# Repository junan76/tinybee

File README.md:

# TINYBEE

This repository contains the hardware design of tinybeef405 flight controller, It supports the latest betaflight firmware currently, you can build your own firmware with the configuration files in the `configs` directory, see the details below.

I personally use this flight controller board as a hardware platform to learn betafight source code and stm32 microcontrollers, related videos were posted on my [Bilibili](https://space.bilibili.com/258537970) account.

## Hardware and Features

- MCU: STM32F405
- IMU: ICM42688-P
- BARO: BMP280
- OSD: BetaFlight OSD, AT7456E
- Blackbox: 128MiB onboard flash, W25Q128JVSIQ
- UARTS: UART2/UART4/UART5
- SWD: Yes
- Digital VTX: Yes
- LEDs: LED0/LED1
- LED Strip: Yes
- Beeper: Yes
- Boot button: For easy entry into DFU mode

## Firmware build and flash

1. Get the latest betaflight source code

```shell
$ git clone https://github.com/betaflight/betaflight.git
$ cd betaflight
$ git submodule init && git submodule update --recursive
```

2. Copy config files

```shell
# download tinybee first, and then...
$ cp -r tinybee/configs/TNBF405 betaflight/src/config/configs
```

3. Build firmware

```shell
$ cd betaflight
$ make arm_sdk_install
$ make TNBF405
# wait until make completes its job, you will get:
$ ls obj
betaflight_2025.12.0-beta_STM32F405_TNBF405.hex  main
# "betaflight_2025.12.0-beta_STM32F405_TNBF405.hex" is what you need
```
4. Flash firmware

    - With [Betaflight Configurator](https://github.com/betaflight/betaflight-configurator/releases) properly installed and opened

    - Connect tinybee flight controlelr via usb

    - Enter DFU mode, press and hold the `BOOT` button, then press the `RESET` button

    - Go to the `Firmware Flasher` tab

    - Load local firmware then flash firmware

5. Basic configurations

    You need to do at least the following setups so that your drone works.

    - `Ports`: select the right ports for RX and VTX
    - `Motors`: make sure the order and direction are both ok
    - `Modes`: how to arm your drone and switch to other modes
    - `VTX`: analog or digital
    - `OSD`: analog or digital

    For more information see [the betalfight wiki](https://www.betaflight.com/docs/wiki/getting-started/setup-guide).
    
    If everything goes well, the final result will be like this:

## Special Thanks

- [The original AcciF405 FC Design](https://oshwlab.com/jesuslg123/f4-v1)
- [Betaflight Project](https://www.betaflight.com/)

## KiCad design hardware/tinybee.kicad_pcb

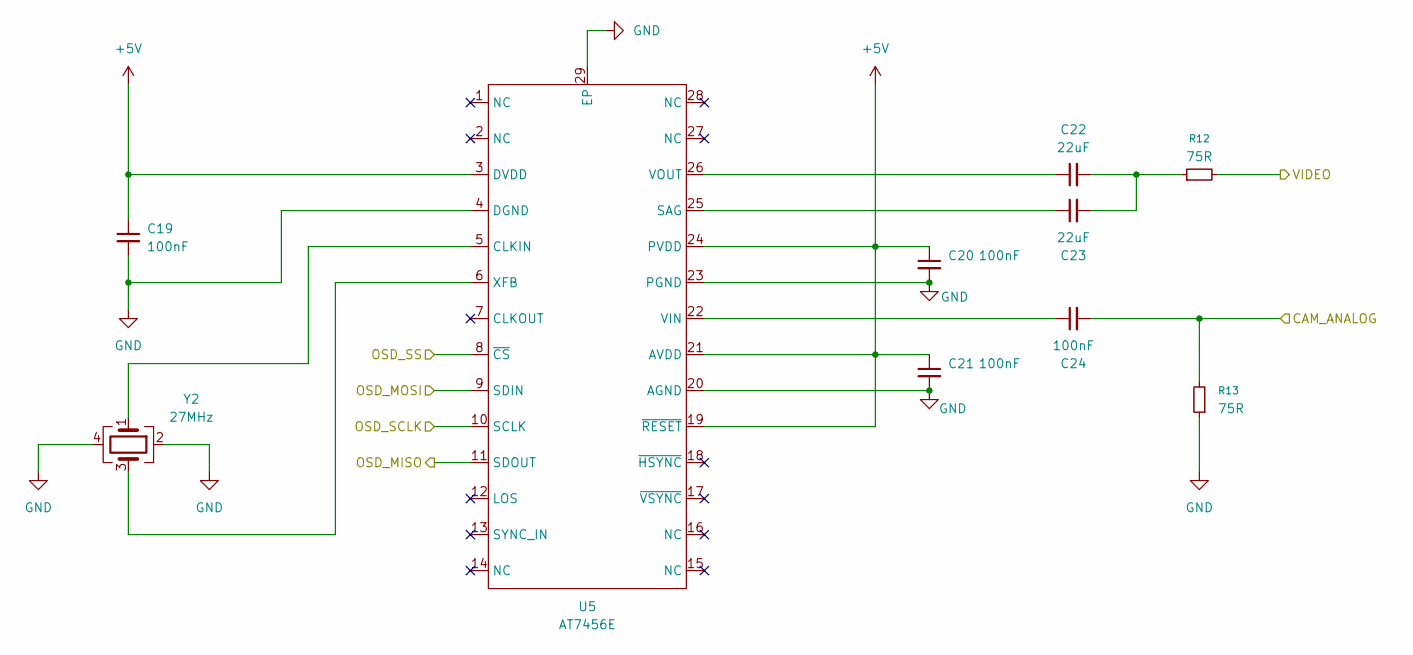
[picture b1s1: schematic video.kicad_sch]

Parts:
C19, C20, C21, C24: 100nF; C_0402_1005Metric; MPN C361198
C22, C23: 22uF; C_0603_1608Metric; MPN C2762594
R12, R13: 75R; R_0402_1005Metric; MPN C25133
U5: AT7456E; TSSOP-28-1EP_4.4x9.7mm_P0.65mm_EP2.85x6.7mm; MPN C82351
Y2: 27MHz; Crystal_SMD_3225-4Pin_3.2x2.5mm; MPN C9008

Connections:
+5V: C19.1, C20.1, C21.1, U5.3 (DVDD), U5.19 (~RESET), U5.21 (AVDD), U5.24 (PVDD); also elsewhere on the board
/CONNECTORS/CAM_ANALOG: C24.2, R13.2; also elsewhere on the board
/CONNECTORS/VIDEO: R12.2; also elsewhere on the board
/MCU/OSD_MISO: U5.11 (SDOUT); also elsewhere on the board
/MCU/OSD_MOSI: U5.9 (SDIN); also elsewhere on the board
/MCU/OSD_SCLK: U5.10 (SCLK); also elsewhere on the board
/MCU/OSD_SS: U5.8 (~CS); also elsewhere on the board
GND: C19.2, C20.2, C21.2, R13.1, U5.4 (DGND), U5.20 (AGND), U5.23 (PGND), U5.29 (EP), Y2.2, Y2.4; also elsewhere on the board
unnamed: C22.2, C23.2, R12.1
unnamed: U5.5 (CLKIN), Y2.1
unnamed: C23.1, U5.25 (SAG)
unnamed: C24.1, U5.22 (VIN)
unnamed: C22.1, U5.26 (VOUT)
unnamed: U5.6 (XFB), Y2.3

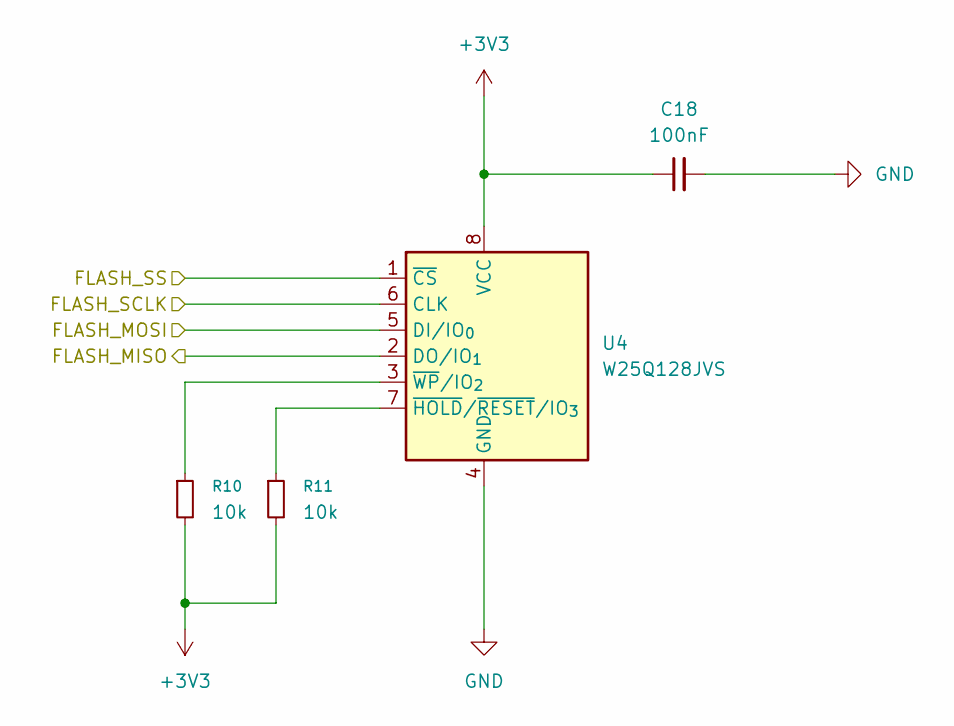
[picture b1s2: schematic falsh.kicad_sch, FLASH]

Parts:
C18: 100nF; C_0402_1005Metric; MPN C361198
R10, R11: 10k; R_0402_1005Metric; MPN C25744
U4: W25Q128JVS; SOIC-8_5.3x5.3mm_P1.27mm; MPN C113767

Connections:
+3V3: C18.1, R10.2, R11.2, U4.8 (VCC); also elsewhere on the board
/FLASH/FLASH_MISO: U4.2 (DO/IO_{1}); also elsewhere on the board
/FLASH/FLASH_MOSI: U4.5 (DI/IO_{0}); also elsewhere on the board
/FLASH/FLASH_SCLK: U4.6 (CLK); also elsewhere on the board
/FLASH/FLASH_SS: U4.1 (~CS); also elsewhere on the board
GND: C18.2, U4.4 (GND); also elsewhere on the board
unnamed: R11.1, U4.7 (~HOLD/~RESET/IO_{3})
unnamed: R10.1, U4.3 (~WP/IO_{2})

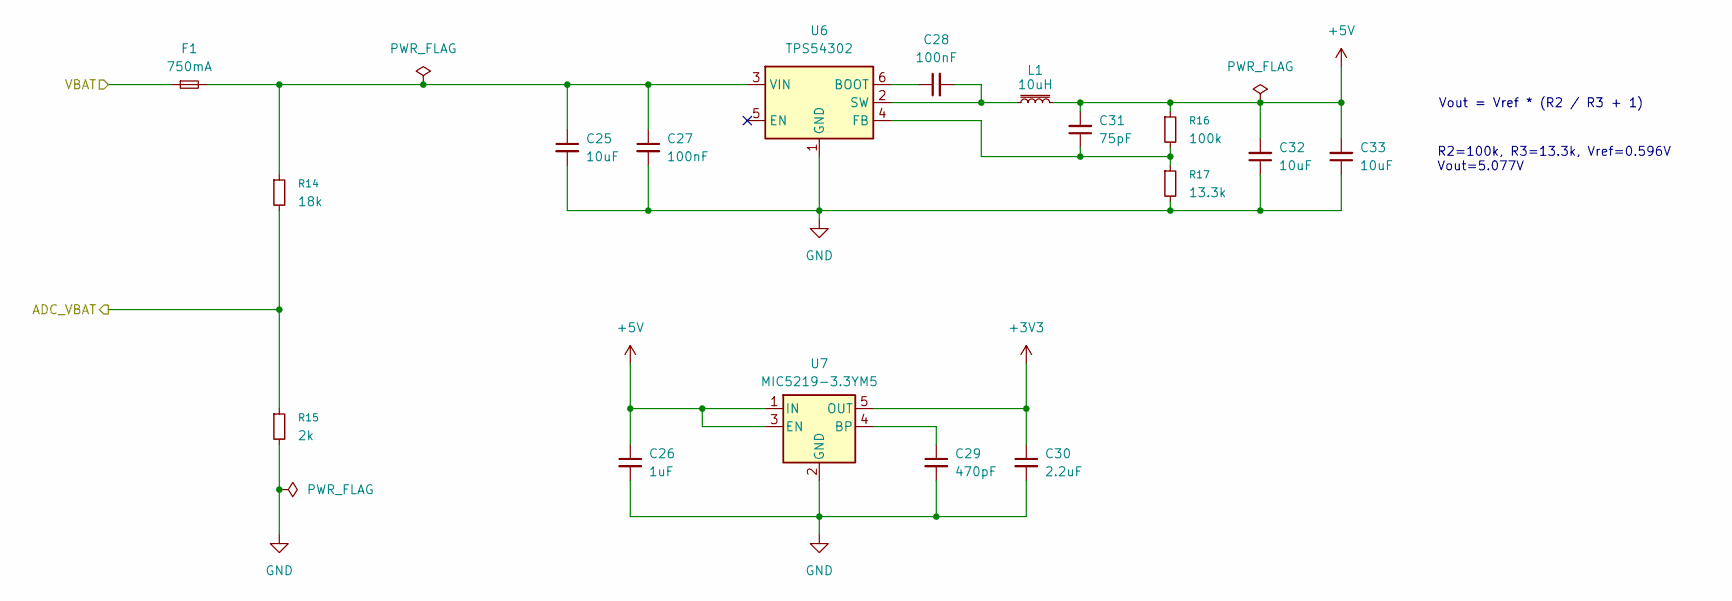
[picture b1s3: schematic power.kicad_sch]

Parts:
C25, C32, C33: 10uF; C_0402_1005Metric; MPN C7472949
C26: 1uF; C_0402_1005Metric; MPN C52923
C27, C28: 100nF; C_0402_1005Metric; MPN C361198
C29: 470pF; C_0402_1005Metric; MPN C1537
C30: 2.2uF; C_0402_1005Metric; MPN C76595
C31: 75pF; C_0402_1005Metric; MPN C107010
F1: 750mA; Fuse_1206_3216Metric; MPN C187594
L1: 10uH; L_Changjiang_FXL0630; MPN C167223
R14: 18k; R_0402_1005Metric; MPN C25762
R15: 2k; R_0402_1005Metric; MPN C4109
R16: 100k; R_0402_1005Metric; MPN C25741
R17: 13.3k; R_0402_1005Metric; MPN C122547
U6: TPS54302; SOT-23-6; MPN C311983
U7: MIC5219-3.3YM5; SOT-23-5; MPN C29613

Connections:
+3V3: C30.1, U7.5 (OUT); also elsewhere on the board
+5V: C26.1, C31.2, C32.2, C33.2, L1.2, R16.1, U7.1 (IN), U7.3 (EN); also elsewhere on the board
/CONNECTORS/VBAT: F1.1; also elsewhere on the board
/MCU/ADC_VBAT: R14.2, R15.1; also elsewhere on the board
GND: C25.2, C26.2, C27.2, C29.2, C30.2, C32.1, C33.1, R15.2, R17.2, U6.1 (GND), U7.2 (GND); also elsewhere on the board
unnamed: C28.1, U6.6 (BOOT)
unnamed: C31.1, R16.2, R17.1, U6.4 (FB)
unnamed: C28.2, L1.1, U6.2 (SW)
unnamed: C25.1, C27.1, F1.2, R14.1, U6.3 (VIN)
unnamed: C29.1, U7.4 (BP)

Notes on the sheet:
R2=100k, R3=13.3k, Vref=0.596V Vout=5.077V
Vout = Vref * (R2 / R3 + 1)

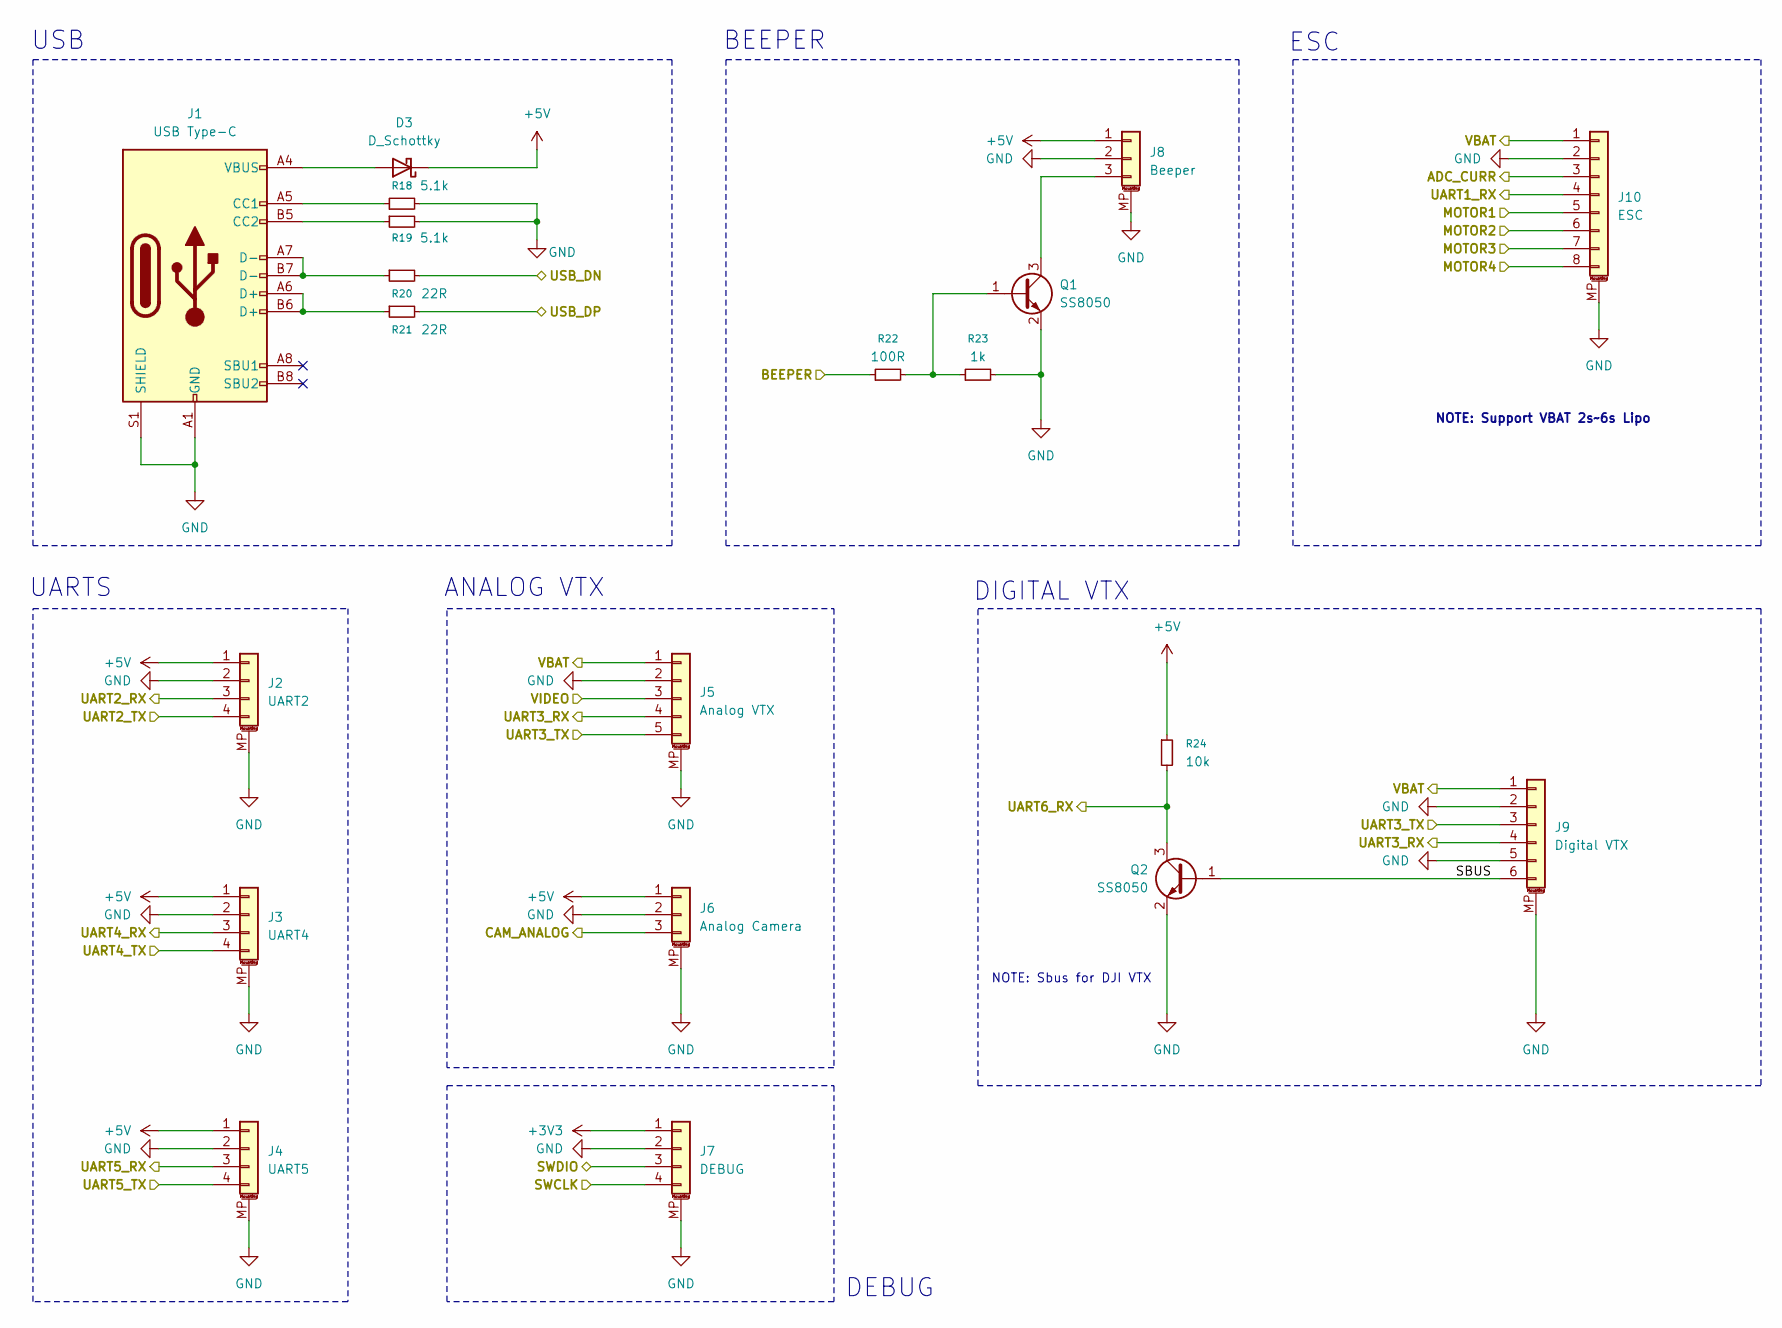
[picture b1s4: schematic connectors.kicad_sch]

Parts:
D3: D_Schottky; D_SMA; MPN C7420369
J1: USB Type-C; USB_C_Receptacle_HCTL_HC-TYPE-C-16P-01A; MPN C3148200
J2: UART2; JST_SH_SM04B-SRSS-TB_1x04-1MP_P1.00mm_Horizontal; MPN C3029343
J3: UART4; JST_SH_SM04B-SRSS-TB_1x04-1MP_P1.00mm_Horizontal; MPN C3029343
J4: UART5; JST_SH_SM04B-SRSS-TB_1x04-1MP_P1.00mm_Horizontal; MPN C3029343
J5: Analog VTX; JST_SH_SM05B-SRSS-TB_1x05-1MP_P1.00mm_Horizontal; MPN C3029344
J6: Analog Camera; JST_SH_SM03B-SRSS-TB_1x03-1MP_P1.00mm_Horizontal; MPN C3029342
J7: DEBUG; JST_SH_SM04B-SRSS-TB_1x04-1MP_P1.00mm_Horizontal; MPN C3029343
J8: Beeper; JST_SH_SM03B-SRSS-TB_1x03-1MP_P1.00mm_Horizontal; MPN C3029342
J9: Digital VTX; JST_SH_SM06B-SRSS-TB_1x06-1MP_P1.00mm_Horizontal; MPN C3029345
J10: ESC; JST_SH_SM08B-SRSS-TB_1x08-1MP_P1.00mm_Horizontal; MPN C3029347
Q1, Q2: SS8050; SOT-23; MPN C7420370
R18, R19: 5.1k; R_0402_1005Metric; MPN C25905
R20, R21: 22R; R_0402_1005Metric; MPN C25092
R22: 100R; R_0402_1005Metric; MPN C25076
R23: 1k; R_0402_1005Metric; MPN C11702
R24: 10k; R_0402_1005Metric; MPN C25744

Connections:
+3V3: J7.1; also elsewhere on the board
+5V: D3.1 (K), J2.1, J3.1, J4.1, J6.1, J8.1, R24.1; also elsewhere on the board
/CONNECTORS/ADC_CURR: J10.3; also elsewhere on the board
/CONNECTORS/BEEPER: R22.1; also elsewhere on the board
/CONNECTORS/CAM_ANALOG: J6.3; also elsewhere on the board
/CONNECTORS/MOTOR1: J10.5; also elsewhere on the board
/CONNECTORS/MOTOR2: J10.6; also elsewhere on the board
/CONNECTORS/MOTOR3: J10.7; also elsewhere on the board
/CONNECTORS/MOTOR4: J10.8; also elsewhere on the board
/CONNECTORS/SBUS: J9.6, Q2.1 (B)
/CONNECTORS/SWCLK: J7.4; also elsewhere on the board
/CONNECTORS/SWDIO: J7.3; also elsewhere on the board
/CONNECTORS/UART1_RX: J10.4; also elsewhere on the board
/CONNECTORS/UART2_RX: J2.3; also elsewhere on the board
/CONNECTORS/UART2_TX: J2.4; also elsewhere on the board
/CONNECTORS/UART3_RX: J5.4, J9.4; also elsewhere on the board
/CONNECTORS/UART3_TX: J5.5, J9.3; also elsewhere on the board
/CONNECTORS/UART4_RX: J3.3; also elsewhere on the board
/CONNECTORS/UART4_TX: J3.4; also elsewhere on the board
/CONNECTORS/UART5_RX: J4.3; also elsewhere on the board
/CONNECTORS/UART5_TX: J4.4; also elsewhere on the board
/CONNECTORS/UART6_RX: Q2.3 (C), R24.2; also elsewhere on the board
/CONNECTORS/USB_DN: R20.2; also elsewhere on the board
/CONNECTORS/USB_DP: R21.2; also elsewhere on the board
/CONNECTORS/VBAT: J5.1, J9.1, J10.1; also elsewhere on the board
/CONNECTORS/VIDEO: J5.3; also elsewhere on the board
GND: J1.A1 (GND), J1.A12 (GND), J1.B1 (GND), J1.B12 (GND), J1.S1 (SHIELD), J2.2, J2.MP (MountPin), J3.2, J3.MP (MountPin), J4.2, J4.MP (MountPin), J5.2, J5.MP (MountPin), J6.2, J6.MP (MountPin), J7.2, J7.MP (MountPin), J8.2, J8.MP (MountPin), J9.2, J9.5, J9.MP (MountPin), J10.2, J10.MP (MountPin), Q1.2 (E), Q2.2 (E), R18.2, R19.2, R23.2; also elsewhere on the board
unnamed: D3.2 (A), J1.A4 (VBUS), J1.A9 (VBUS), J1.B4 (VBUS), J1.B9 (VBUS)
unnamed: J1.A5 (CC1), R18.1
unnamed: J1.B5 (CC2), R19.1
unnamed: J1.A6 (D+), J1.B6 (D+), R21.1
unnamed: J1.A7 (D-), J1.B7 (D-), R20.1
unnamed: J8.3, Q1.3 (C)
unnamed: Q1.1 (B), R22.2, R23.1

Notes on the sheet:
ANALOG VTX
DEBUG
DIGITAL VTX
BEEPER
USB
ESC
UARTS
NOTE: Sbus for DJI VTX
NOTE: Support VBAT 2s~6s Lipo

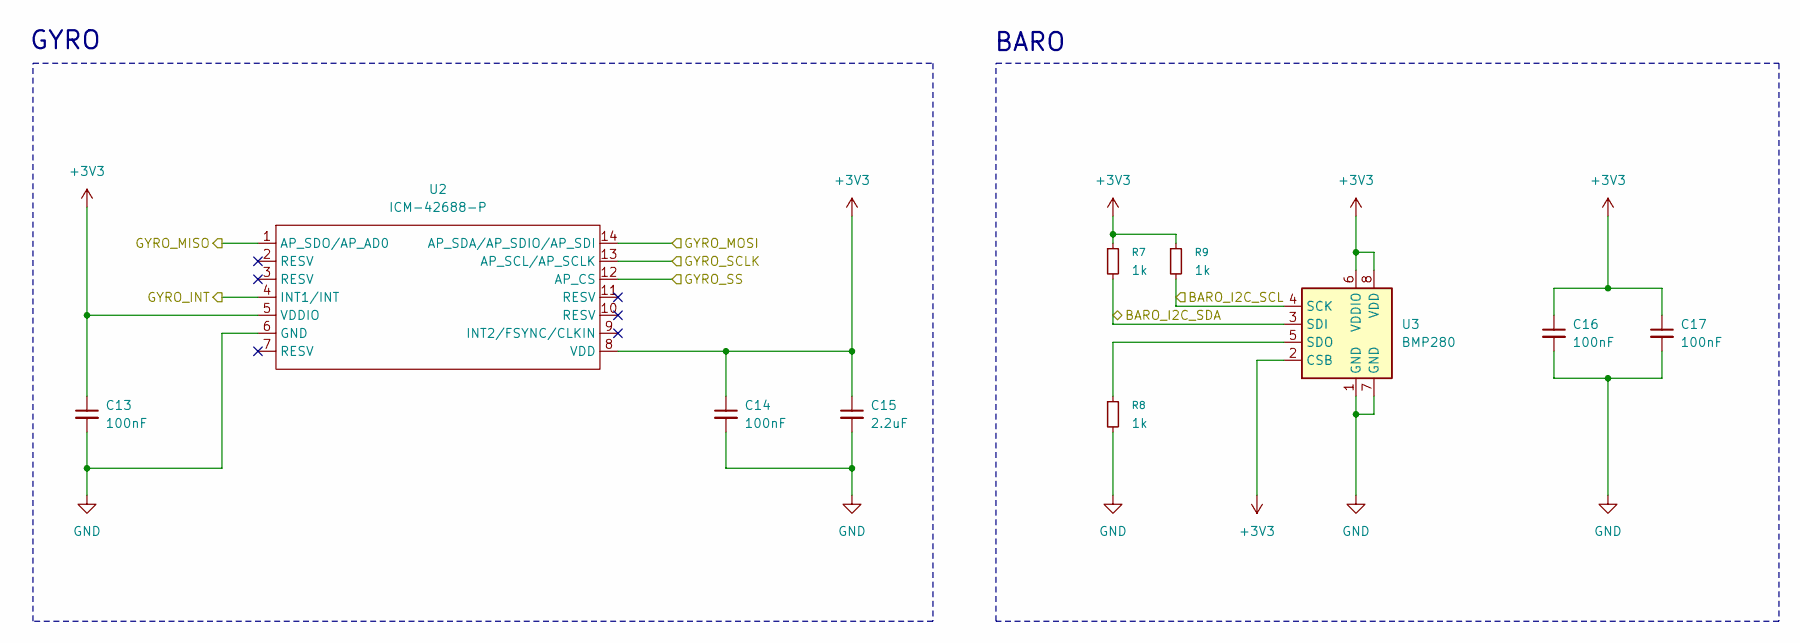
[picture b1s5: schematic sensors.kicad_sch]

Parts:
C13, C14, C16, C17: 100nF; C_0402_1005Metric; MPN C361198
C15: 2.2uF; C_0402_1005Metric; MPN C76595
R7, R8, R9: 1k; R_0402_1005Metric; MPN C11702
U2: ICM-42688-P; LGA-14_3x2.5mm_P0.5mm_LayoutBorder3x4y; MPN C1850418
U3: BMP280; Bosch_LGA-8_2x2.5mm_P0.65mm_ClockwisePinNumbering; MPN C83291

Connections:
+3V3: C13.1, C14.1, C15.1, C16.1, C17.1, R7.1, R9.1, U2.5 (VDDIO), U2.8 (VDD), U3.2 (CSB), U3.6 (VDDIO), U3.8 (VDD); also elsewhere on the board
/MCU/GYRO_INT: U2.4 (INT1/INT); also elsewhere on the board
/MCU/GYRO_MISO: U2.1 (AP_SDO/AP_AD0); also elsewhere on the board
/MCU/GYRO_MOSI: U2.14 (AP_SDA/AP_SDIO/AP_SDI); also elsewhere on the board
/MCU/GYRO_SCLK: U2.13 (AP_SCL/AP_SCLK); also elsewhere on the board
/MCU/GYRO_SS: U2.12 (AP_CS); also elsewhere on the board
/MCU/I2C1_SCL: R9.2, U3.4 (SCK); also elsewhere on the board
/MCU/I2C1_SDA: R7.2, U3.3 (SDI); also elsewhere on the board
GND: C13.2, C14.2, C15.2, C16.2, C17.2, R8.2, U2.6 (GND), U3.1 (GND), U3.7 (GND); also elsewhere on the board
unnamed: R8.1, U3.5 (SDO)

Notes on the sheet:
BARO
GYRO

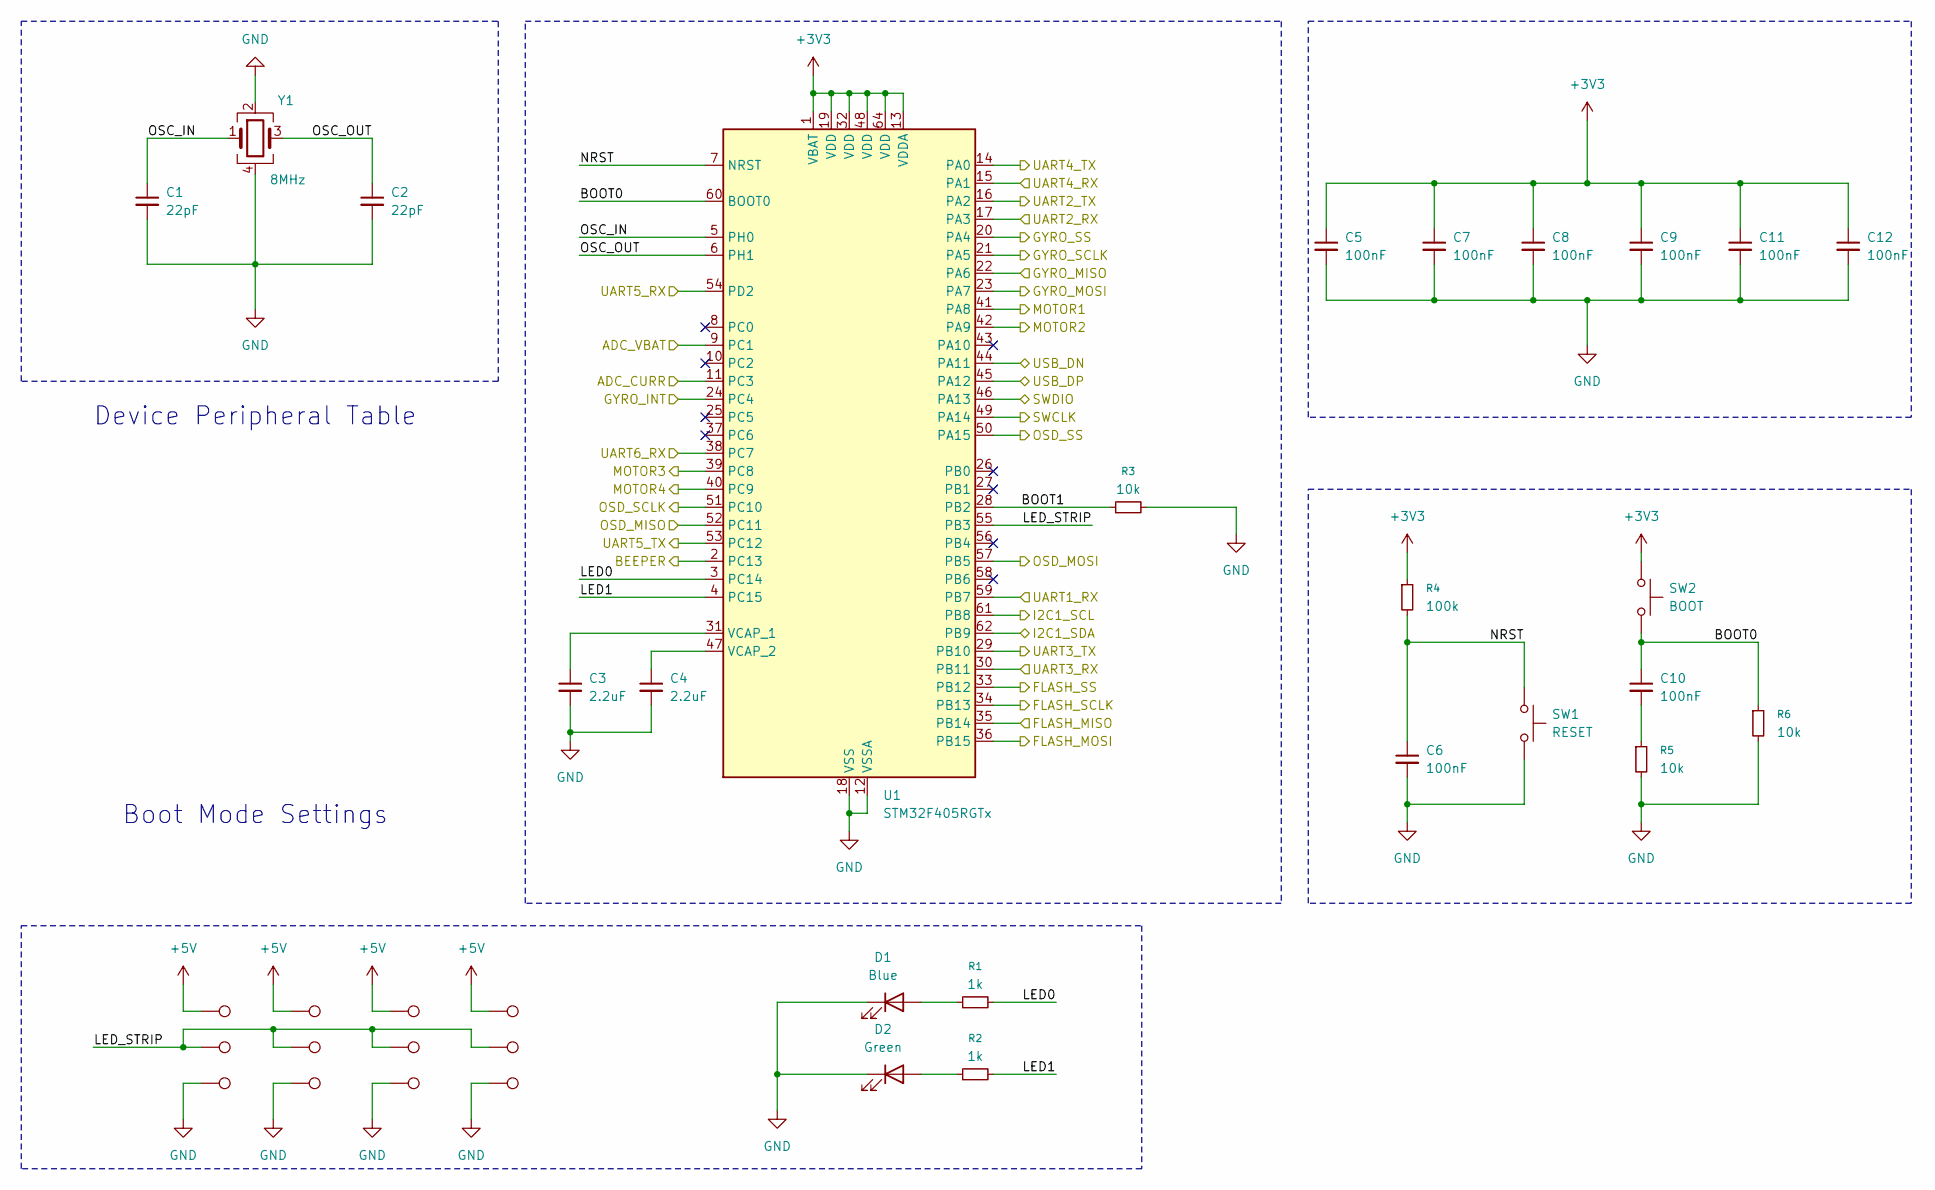
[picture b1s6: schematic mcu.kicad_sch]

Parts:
C1, C2: 22pF; C_0402_1005Metric; MPN C1555
C3, C4: 2.2uF; C_0402_1005Metric; MPN C76595
C5, C6, C7, C8, C9, C10, C11, C12: 100nF; C_0402_1005Metric; MPN C361198
D1: Blue; LED_0402_1005Metric; MPN C434447
D2: Green; LED_0402_1005Metric; MPN C434446
G1, G2, G3, G4: TestPoint; TestPoint_Pad_D1.0mm
P1, P2, P3, P4: TestPoint; TestPoint_Pad_D1.0mm
R1, R2: 1k; R_0402_1005Metric; MPN C11702
R3, R5, R6: 10k; R_0402_1005Metric; MPN C25744
R4: 100k; R_0402_1005Metric; MPN C25741
S1, S2, S3, S4: TestPoint; TestPoint_Pad_D1.0mm
SW1: RESET; TS3425BA; MPN C2681476
SW2: BOOT; TS3425BA; MPN C2681476
U1: STM32F405RGTx; LQFP-64_10x10mm_P0.5mm; MPN C15742
Y1: 8MHz; Crystal_SMD_3225-4Pin_3.2x2.5mm; MPN C2682775

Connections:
+3V3: C5.1, C7.1, C8.1, C9.1, C11.1, C12.1, R4.1, SW2.1, U1.1 (VBAT), U1.13 (VDDA), U1.19 (VDD), U1.32 (VDD), U1.48 (VDD), U1.64 (VDD); also elsewhere on the board
+5V: P1.1, P2.1, P3.1, P4.1; also elsewhere on the board
/CONNECTORS/ADC_CURR: U1.11 (PC3); also elsewhere on the board
/CONNECTORS/BEEPER: U1.2 (PC13); also elsewhere on the board
/CONNECTORS/MOTOR1: U1.41 (PA8); also elsewhere on the board
/CONNECTORS/MOTOR2: U1.42 (PA9); also elsewhere on the board
/CONNECTORS/MOTOR3: U1.39 (PC8); also elsewhere on the board
/CONNECTORS/MOTOR4: U1.40 (PC9); also elsewhere on the board
/CONNECTORS/SWCLK: U1.49 (PA14); also elsewhere on the board
/CONNECTORS/SWDIO: U1.46 (PA13); also elsewhere on the board
/CONNECTORS/UART1_RX: U1.59 (PB7); also elsewhere on the board
/CONNECTORS/UART2_RX: U1.17 (PA3); also elsewhere on the board
/CONNECTORS/UART2_TX: U1.16 (PA2); also elsewhere on the board
/CONNECTORS/UART3_RX: U1.30 (PB11); also elsewhere on the board
/CONNECTORS/UART3_TX: U1.29 (PB10); also elsewhere on the board
/CONNECTORS/UART4_RX: U1.15 (PA1); also elsewhere on the board
/CONNECTORS/UART4_TX: U1.14 (PA0); also elsewhere on the board
/CONNECTORS/UART5_RX: U1.54 (PD2); also elsewhere on the board
/CONNECTORS/UART5_TX: U1.53 (PC12); also elsewhere on the board
/CONNECTORS/UART6_RX: U1.38 (PC7); also elsewhere on the board
/CONNECTORS/USB_DN: U1.44 (PA11); also elsewhere on the board
/CONNECTORS/USB_DP: U1.45 (PA12); also elsewhere on the board
/FLASH/FLASH_MISO: U1.35 (PB14); also elsewhere on the board
/FLASH/FLASH_MOSI: U1.36 (PB15); also elsewhere on the board
/FLASH/FLASH_SCLK: U1.34 (PB13); also elsewhere on the board
/FLASH/FLASH_SS: U1.33 (PB12); also elsewhere on the board
/MCU/ADC_VBAT: U1.9 (PC1); also elsewhere on the board
/MCU/BOOT0: C10.1, R6.1, SW2.2, U1.60 (BOOT0)
/MCU/BOOT1: R3.1, U1.28 (PB2)
/MCU/GYRO_INT: U1.24 (PC4); also elsewhere on the board
/MCU/GYRO_MISO: U1.22 (PA6); also elsewhere on the board
/MCU/GYRO_MOSI: U1.23 (PA7); also elsewhere on the board
/MCU/GYRO_SCLK: U1.21 (PA5); also elsewhere on the board
/MCU/GYRO_SS: U1.20 (PA4); also elsewhere on the board
/MCU/I2C1_SCL: U1.61 (PB8); also elsewhere on the board
/MCU/I2C1_SDA: U1.62 (PB9); also elsewhere on the board
/MCU/LED0: R1.2, U1.3 (PC14)
/MCU/LED1: R2.2, U1.4 (PC15)
/MCU/LED_STRIP: S1.1, S2.1, S3.1, S4.1, U1.55 (PB3)
/MCU/NRST: C6.1, R4.2, SW1.1, U1.7 (NRST)
/MCU/OSC_IN: C1.1, U1.5 (PH0), Y1.1
/MCU/OSC_OUT: C2.1, U1.6 (PH1), Y1.3
/MCU/OSD_MISO: U1.52 (PC11); also elsewhere on the board
/MCU/OSD_MOSI: U1.57 (PB5); also elsewhere on the board
/MCU/OSD_SCLK: U1.51 (PC10); also elsewhere on the board
/MCU/OSD_SS: U1.50 (PA15); also elsewhere on the board
GND: C1.2, C2.2, C3.2, C4.2, C5.2, C6.2, C7.2, C8.2, C9.2, C11.2, C12.2, D1.1 (K), D2.1 (K), G1.1, G2.1, G3.1, G4.1, R3.2, R5.2, R6.2, SW1.2, U1.12 (VSSA), U1.18 (VSS), U1.63 (VSS), Y1.2, Y1.4; also elsewhere on the board
unnamed: C10.2, R5.1
unnamed: D1.2 (A), R1.1
unnamed: D2.2 (A), R2.1
unnamed: C3.1, U1.31 (VCAP_1)
unnamed: C4.1, U1.47 (VCAP_2)

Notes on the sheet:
Device Peripheral Table
Boot Mode Settings

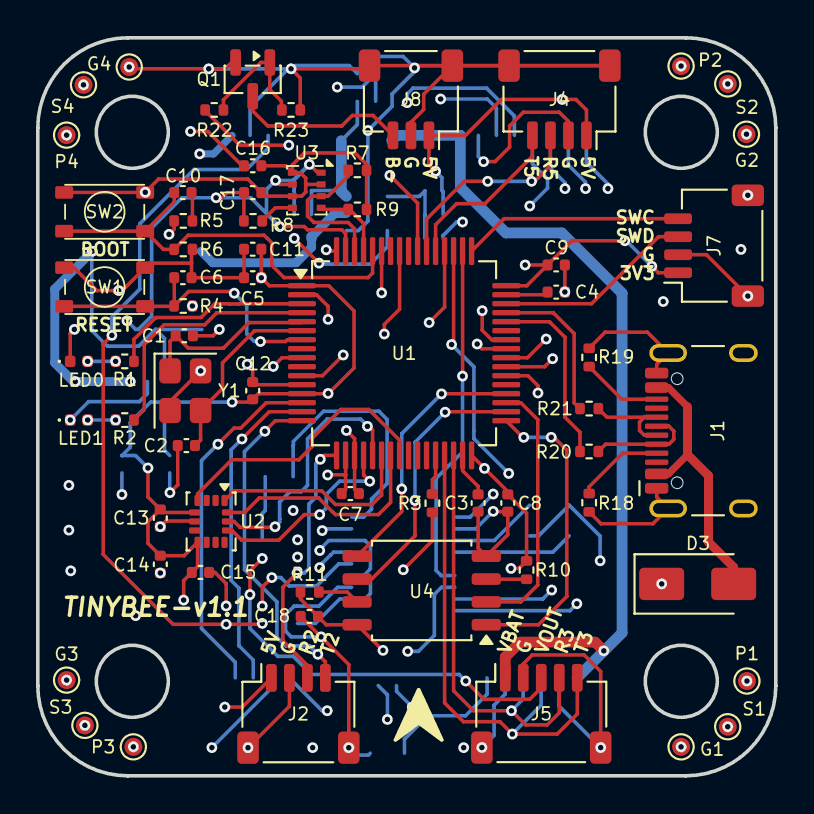
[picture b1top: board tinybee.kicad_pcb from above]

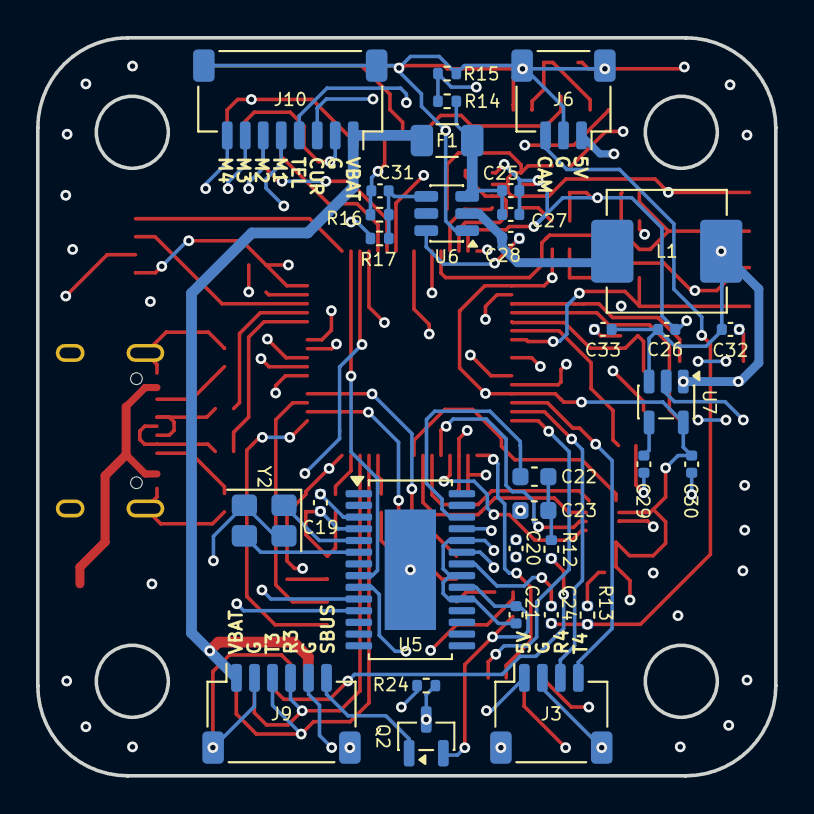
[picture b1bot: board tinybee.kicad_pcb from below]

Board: 4 copper layers, 41.0 x 41.0 mm, 97 parts (33 on the bottom side), 77 nets.

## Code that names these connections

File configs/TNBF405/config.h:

/*
 * This file is part of Betaflight.
 *
 * Betaflight is free software. You can redistribute this software
 * and/or modify this software under the terms of the GNU General
 * Public License as published by the Free Software Foundation,
 * either version 3 of the License, or (at your option) any later
 * version.
 *
 * Betaflight is distributed in the hope that it will be useful,
 * but WITHOUT ANY WARRANTY; without even the implied warranty of
 * MERCHANTABILITY or FITNESS FOR A PARTICULAR PURPOSE.
 *
 * See the GNU General Public License for more details.
 *
 * You should have received a copy of the GNU General Public
 * License along with this software.
 *
 * If not, see <http://www.gnu.org/licenses/>.
 */

#pragma once

#define FC_TARGET_MCU     STM32F405

#define BOARD_NAME        TNBF405
#define MANUFACTURER_ID   TINYBEE

#define USE_ACC
#define USE_GYRO

#define USE_ACC_SPI_ICM42688P // For ICM42688P variation
#define USE_GYRO_SPI_ICM42688P // For ICM42688P variation

#define USE_BARO
#define USE_BARO_BMP280

#define USE_FLASH
#define USE_FLASH_M25P16
#define USE_FLASH_W25Q128FV
#define USE_FLASH_W25N01G

#define USE_MAX7456

// I/O
#define LED0_PIN             PC14
#define LED1_PIN             PC15
#define BEEPER_PIN           PC13
#define BEEPER_INVERTED
#define LED_STRIP_PIN        PB3

// ACC/GYRO SPI 1
#define USE_SPI_GYRO
#define GYRO_1_EXTI_PIN      PC4
#define GYRO_1_CS_PIN        PA4
#define GYRO_1_SPI_INSTANCE  SPI1
#define GYRO_1_ALIGN CW180_DEG

#define SPI1_SCK_PIN         PA5
#define SPI1_SDI_PIN         PA6
#define SPI1_SDO_PIN         PA7

// FLASH SPI 2
#define SPI2_SCK_PIN         PB13
#define SPI2_SDI_PIN         PB14
#define SPI2_SDO_PIN         PB15

#define FLASH_CS_PIN         PB12
#define FLASH_SPI_INSTANCE   SPI2

// OSD SPI 3
#define SPI3_SCK_PIN         PC10
#define SPI3_SDI_PIN         PC11
#define SPI3_SDO_PIN         PB5

#define MAX7456_SPI_CS_PIN   PA15
#define MAX7456_SPI_INSTANCE SPI3

// ADC
#define USE_ADC
#define ADC_VBAT_PIN         PC1
#define ADC_CURR_PIN         PC3
#define ADC_INSTANCE         ADC1

// UART PORTS
#define UART1_TX_PIN         PB6
#define UART1_RX_PIN         PB7

#define UART2_TX_PIN         PA2
#define UART2_RX_PIN         PA3

#define UART3_TX_PIN         PB10
#define UART3_RX_PIN         PB11

#define UART4_TX_PIN         PA0
#define UART4_RX_PIN         PA1

#define UART5_TX_PIN         PC12
#define UART5_RX_PIN         PD2

#define UART6_TX_PIN         PC6
#define UART6_RX_PIN         PC7

// TIMERS
#define TIMER_PIN_MAPPING \
    TIMER_PIN_MAP( 0, PA8 , 1,  1) \
    TIMER_PIN_MAP( 1, PA9 , 1,  1) \
    TIMER_PIN_MAP( 2, PC8 , 1,  0) \
    TIMER_PIN_MAP( 3, PC9 , 1,  0) \
    TIMER_PIN_MAP( 4, PB3 , 1,  0)

// MOTORS PINOUT
#define MOTOR1_PIN           PA8
#define MOTOR2_PIN           PA9
#define MOTOR3_PIN           PC8
#define MOTOR4_PIN           PC9

#define ADC1_DMA_OPT         1

// BARO I2C
#define BARO_I2C_INSTANCE I2CDEV_1
#define MAG_I2C_INSTANCE I2CDEV_1

#define I2C1_SCL_PIN         PB8
#define I2C1_SDA_PIN         PB9

// DEFAULTS
#define DEFAULT_BLACKBOX_DEVICE         BLACKBOX_DEVICE_FLASH
#define DEFAULT_CURRENT_METER_SOURCE    CURRENT_METER_ADC
#define DEFAULT_VOLTAGE_METER_SOURCE    VOLTAGE_METER_ADC
#define DEFAULT_VOLTAGE_METER_SCALE     102
#define DEFAULT_DSHOT_BURST DSHOT_DMAR_OFF
#define DEFAULT_DSHOT_BITBANG DSHOT_BITBANG_OFF

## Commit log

2025-11-22 tinybee: hardware design and project introduction.
2025-11-27 update readme, add final pcb image.
